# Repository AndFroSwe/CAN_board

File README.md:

# CAN_board
CAN interface board based on the MCP2515 and MCP2551

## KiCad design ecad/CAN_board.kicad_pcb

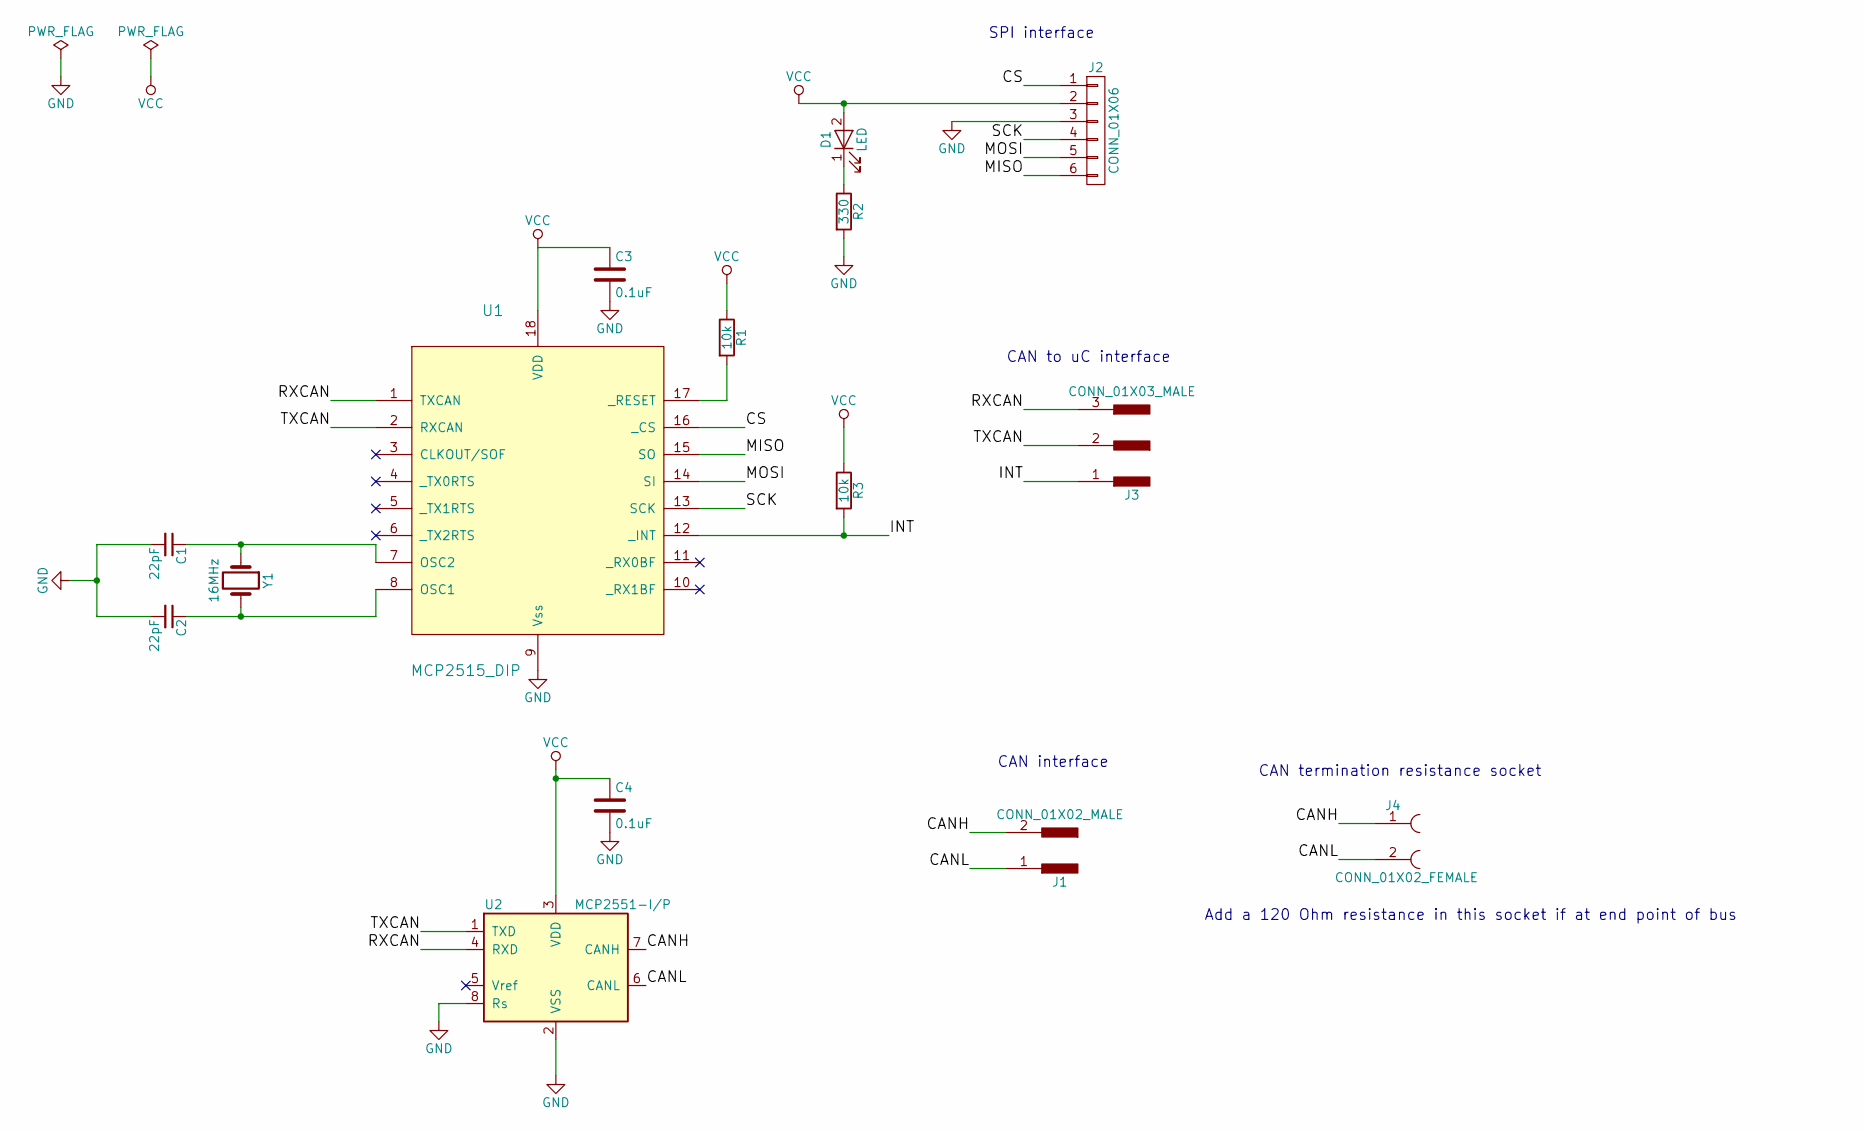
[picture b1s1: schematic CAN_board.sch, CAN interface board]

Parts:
C1, C2: 22pF; C_Disc_D3.8mm_W2.6mm_P2.50mm
C3, C4: 0.1uF; C_Rect_L4.0mm_W2.5mm_P2.50mm
D1: LED; LED_D4.0mm
J1: CONN_01X02_MALE; Socket_Strip_Straight_2x01_Pitch2.54mm
J2: CONN_01X06; Socket_Strip_Straight_1x06_Pitch2.54mm
J3: CONN_01X03_MALE; Socket_Strip_Straight_1x03_Pitch2.54mm
J4: CONN_01X02_FEMALE; Socket_Strip_Straight_2x01_Pitch2.54mm
R1, R3: 10k; R_Axial_DIN0414_L11.9mm_D4.5mm_P5.08mm_Vertical
R2: 330; R_Axial_DIN0414_L11.9mm_D4.5mm_P5.08mm_Vertical
U1: MCP2515_DIP; DIP-18_W7.62mm
U2: MCP2551-I/P; DIP-8_W7.62mm
Y1: 16MHz; Crystal_HC18-U_Vertical

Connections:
/CANH: J1.2, J4.1, U2.7 (CANH)
/CANL: J1.1, J4.2, U2.6 (CANL)
/CS: J2.1, U1.16 (_CS)
/INT: J3.1, R3.2, U1.12 (_INT)
/MISO: J2.6, U1.15 (SO)
/MOSI: J2.5, U1.14 (SI)
/RXCAN: J3.3, U1.1 (TXCAN), U2.4 (RXD)
/SCK: J2.4, U1.13 (SCK)
/TXCAN: J3.2, U1.2 (RXCAN), U2.1 (TXD)
GND: C1.2, C2.2, C3.2, C4.2, J2.3, R2.2, U1.9 (Vss), U2.2 (VSS), U2.8 (Rs)
unnamed: C1.1, U1.7 (OSC2), Y1.1
unnamed: C2.1, U1.8 (OSC1), Y1.2
unnamed: D1.1 (K), R2.1
unnamed: R1.2, U1.17 (_RESET)
VCC: C3.1, C4.1, D1.2 (A), J2.2, R1.1, R3.1, U1.18 (VDD), U2.3 (VDD)

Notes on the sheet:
SPI interface
CAN to uC interface
CAN interface
CAN termination resistance socket
Add a 120 Ohm resistance in this socket if at end point of bus

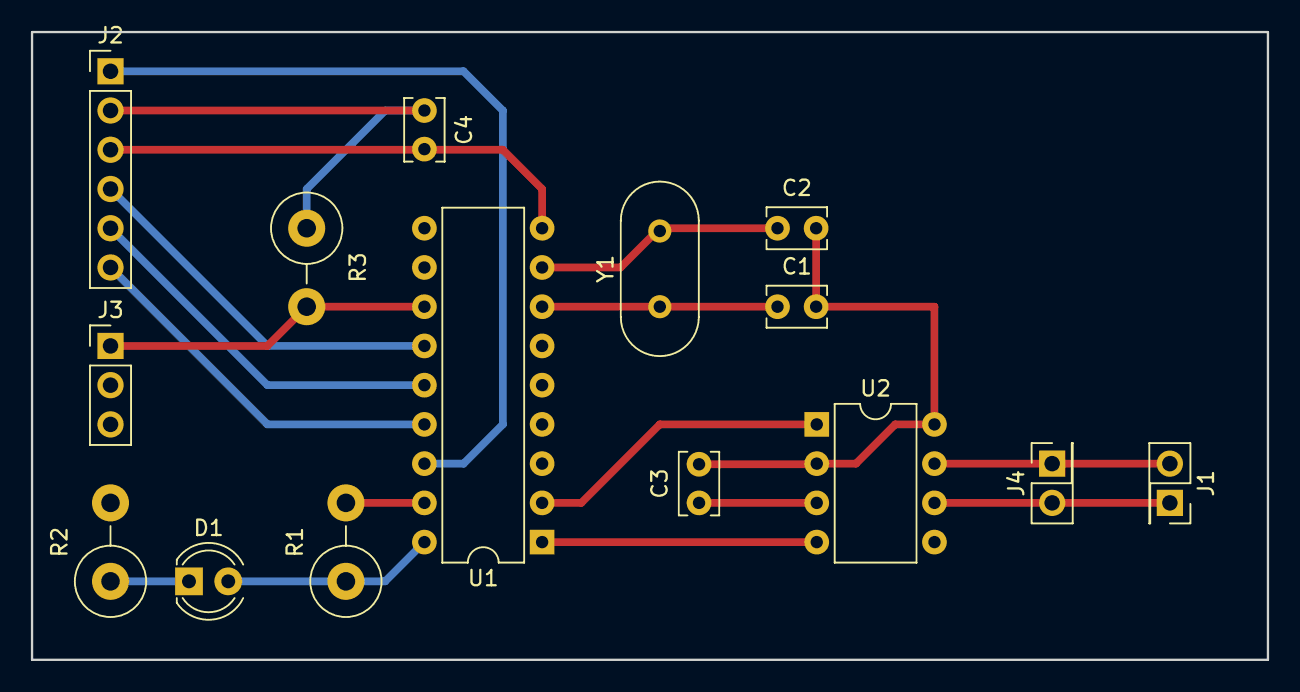
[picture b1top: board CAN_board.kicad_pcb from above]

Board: 2 copper layers, 80.0 x 40.6 mm, 15 parts (0 on the bottom side), 15 nets.

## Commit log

2017-10-29 Initial commit. Made a first version of ecad. Needs improvement
